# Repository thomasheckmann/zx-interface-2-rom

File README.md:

# ZX Interface 2 custom multi ROM catridge
Another custom ROM cartridge for ZX Interface 2, supporting 256kb EPROM with manual ROM selection using switch. The 256kb EPROM can hold up to 4 16kb banks, which is selectable with a switch combination.
This cartridge only supports 16KB images and manual bank switch and no paging out - it behaves just as the original ROM catridges.

## Schema and PCB version 1
Just a simple schema created with KiCad from description of original Interface 2 and Roms as found on the internet.

| SCHEMA | PCB |
| ------ | --- |
|||

Assembled the cartridge looks like this

## PCB version 1.1
Even that the first version of the PBC works ok, a few errors was made - but again I'm new to KiCad, so I'm slowly learning :-)

- Most important error is that I forgot to check the pads, I simply forgot to check that the pads are added to the solder mask layer! So as can be seen on the image, I had to carefully scrabe the surface - for the pads to be visible.

- The switch are "mirrored" in my oppinion, I would expect the left switch to be the most significant bit (MSB) - so another change for next version.

- Slot in connector turned out to be a bit too narrow, so I had to make it a bit wider.

- If you look closely vias are placed between the connector pads, in next version that will be avoided - by adding safe zones between all pads.

- Resistor value changed from 4K7 to 10K, suggested as the EEPROM is CMOS and not TTL.

- EEPROM rotated so it has same orientation as the other IC (stupid yes, but important to some like me)

- Changed PCB from 4 to 2 layers (Only used 4 to reduces the number of vias created between pads)

With these changes version 1.1 of this little PCB ends up like this:

| <!---> | <!---> |
| ------ | ------ |
|||

And here how it looks like when build and attached to a ZX Spectrum

| <!---> | <!---> |
| ------ | ------ |
|||

## How to create image for EEPROM
The W27C512 EEPROM can contain 4 x 16Kb images - selectable with the switch, forming the binary number 0-3 of the bank active.

For Windows
```
COPY /B ROM_3+ROM_2+ROM_1+ROM_0 IMAGE.BIN
```
Use your favorite (E)EPROM programmer to transfer the IMAGE.BIN to the EEPROM

```
LEFT|RIGHT
OFF | OFF - 0: ROM_0
OFF | ON  - 1: ROM_1
ON  | OFF - 2: ROM_2
ON  | ON  - 3: ROM_3
```
## PCB version 1.2
Only small changes to v1.2 of the board, which I think now can be considered final.

- Changed from pull-ups to pull-downs, to match actual behaviour of DIP-SWITCH (up = 1/ON/HIGH, down = 0/OFF/LOW)
- Made PADS 2mm longer, as some connectors might have issues with the smaller size

| SCHEMA | PCB |
| ------ | --- |
|||

## How to create image for EEPROM
The W27C512 EEPROM can contain 4 x 16Kb images - selectable with the switch, forming the binary number 0-3 of the bank active.

For Windows
```
COPY /B ROM_0+ROM_1+ROM_2+ROM_3 IMAGE.BIN
```
Use your favorite (E)EPROM programmer to transfer the IMAGE.BIN to the EEPROM
```
LEFT|RIGHT
OFF | OFF - 0: ROM_0
OFF | ON  - 1: ROM_1
ON  | OFF - 2: ROM_2
ON  | ON  - 3: ROM_3
```

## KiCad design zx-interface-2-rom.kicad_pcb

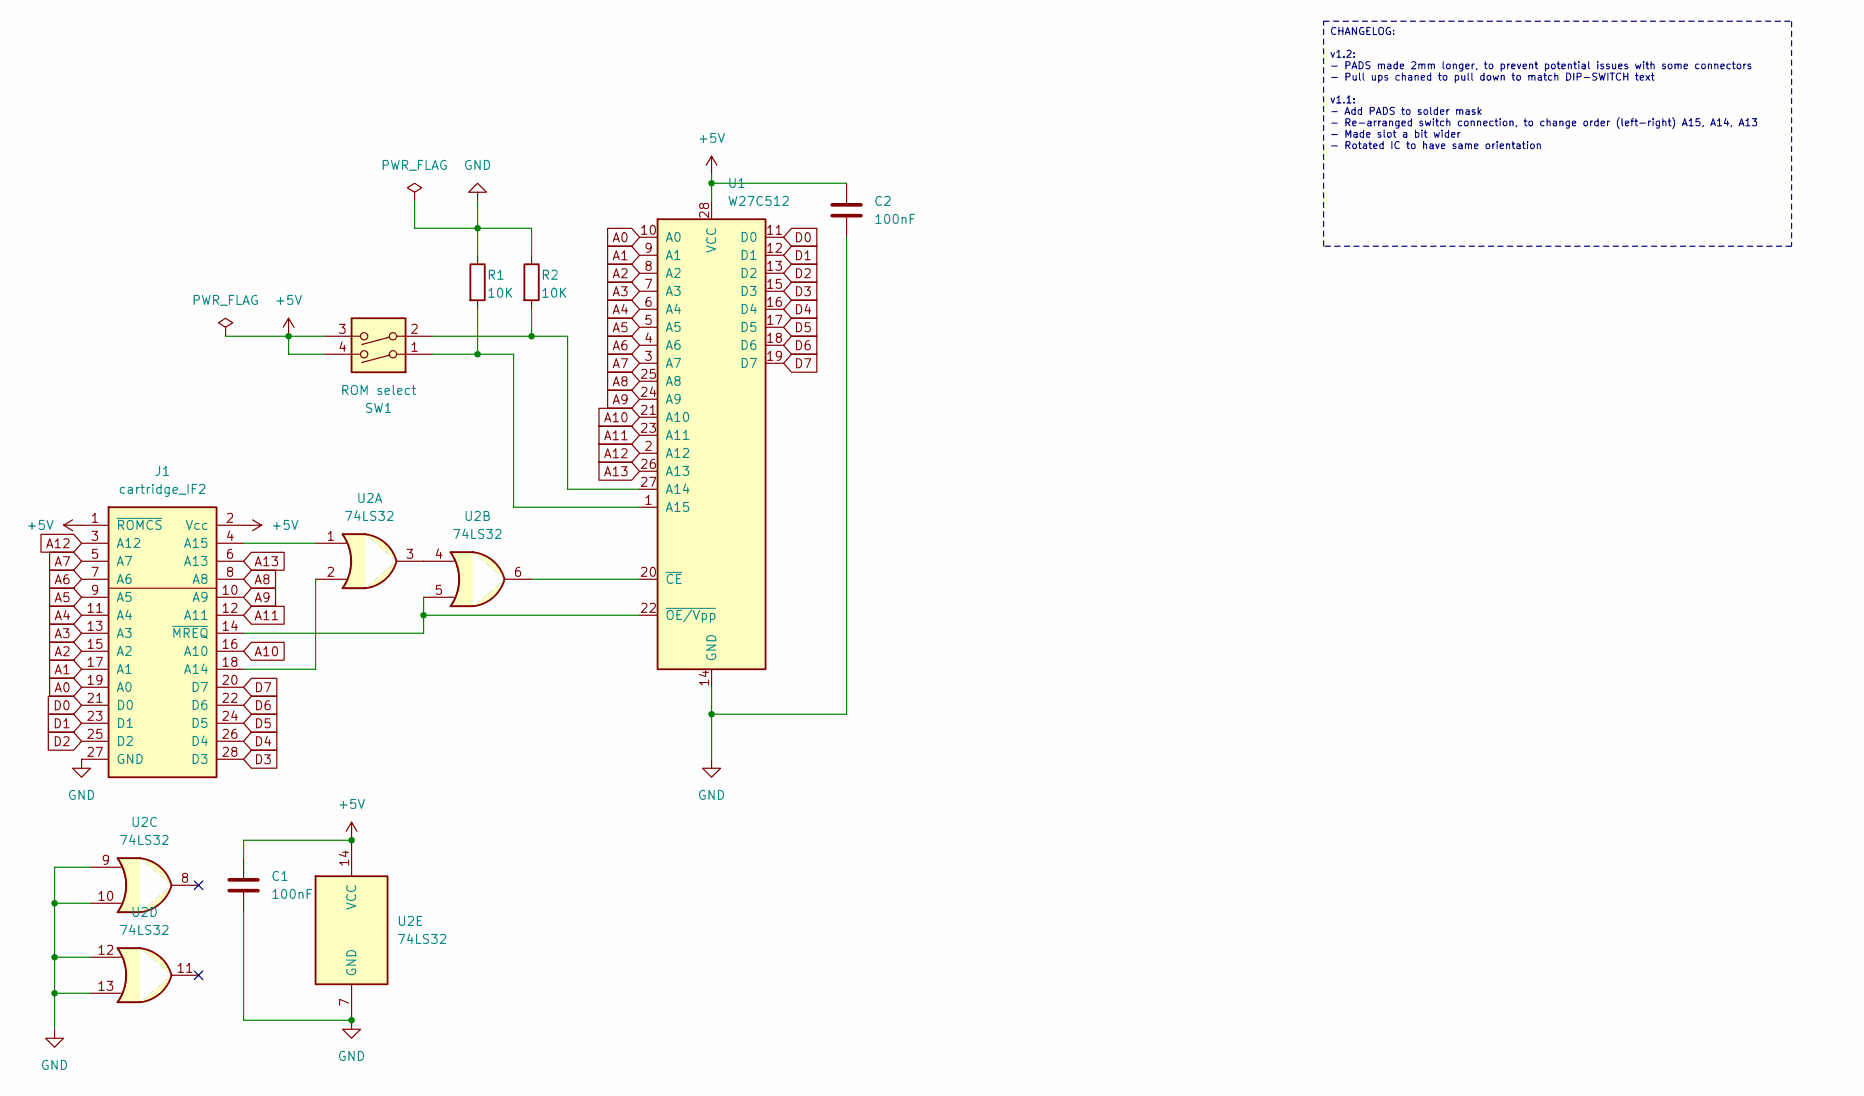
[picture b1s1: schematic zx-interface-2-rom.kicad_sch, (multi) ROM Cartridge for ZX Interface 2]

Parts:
C1, C2: 100nF; C_Disc_D3.0mm_W1.6mm_P2.50mm
J1: cartridge_IF2; CART_IF2_EDGE
R1, R2: 10K; R_Axial_DIN0207_L6.3mm_D2.5mm_P10.16mm_Horizontal
SW1: ROM select; SW_DIP_SPSTx02_Slide_6.7x6.64mm_W7.62mm_P2.54mm_LowProfile
U1: W27C512; DIP-28_W15.24mm_Socket
U2: 74LS32; DIP-14_W7.62mm_Socket

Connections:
+5V: C1.1, C2.1, J1.1 (~ROMCS), J1.2 (Vcc), SW1.3, SW1.4, U1.28 (VCC), U2.14 (VCC)
A0: J1.19 (A0), U1.10 (A0)
A1: J1.17 (A1), U1.9 (A1)
A2: J1.15 (A2), U1.8 (A2)
A3: J1.13 (A3), U1.7 (A3)
A4: J1.11 (A4), U1.6 (A4)
A5: J1.9 (A5), U1.5 (A5)
A6: J1.7 (A6), U1.4 (A6)
A7: J1.5 (A7), U1.3 (A7)
A8: J1.8 (A8), U1.25 (A8)
A9: J1.10 (A9), U1.24 (A9)
A10: J1.16 (A10), U1.21 (A10)
A11: J1.12 (A11), U1.23 (A11)
A12: J1.3 (A12), U1.2 (A12)
A13: J1.6 (A13), U1.26 (A13)
D0: J1.21 (D0), U1.11 (D0)
D1: J1.23 (D1), U1.12 (D1)
D2: J1.25 (D2), U1.13 (D2)
D3: J1.28 (D3), U1.15 (D3)
D4: J1.26 (D4), U1.16 (D4)
D5: J1.24 (D5), U1.17 (D5)
D6: J1.22 (D6), U1.18 (D6)
D7: J1.20 (D7), U1.19 (D7)
GND: C1.2, C2.2, J1.27 (GND), R1.1, R2.1, U1.14 (GND), U2.7 (GND), U2.9, U2.10, U2.12, U2.13
unnamed: J1.18 (A14), U2.2
unnamed: J1.4 (A15), U2.1
unnamed: J1.14 (~MREQ), U1.22 (~OE/Vpp), U2.5
unnamed: R2.2, SW1.2, U1.27 (A14)
unnamed: R1.2, SW1.1, U1.1 (A15)
unnamed: U1.20 (~CE), U2.6
unnamed: U2.3, U2.4

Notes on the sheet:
CHANGELOG: v1.2: - PADS made 2mm longer, to prevent potential issues with some connectors - Pull ups chaned to pull down to match DIP-SWITCH text v1.1: - Add PADS to solder mask - Re-arranged switch connection, to change order (left-right) A15, A14, A13 - Made slot a bit wider - Rotated IC to have 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

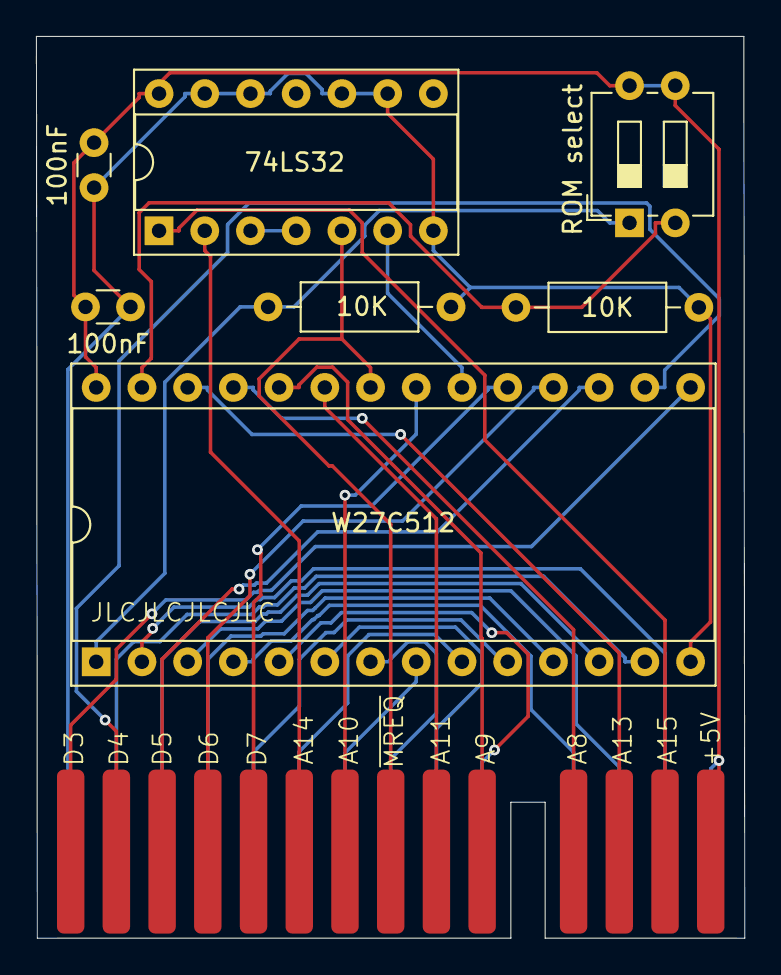
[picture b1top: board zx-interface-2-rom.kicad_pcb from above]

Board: 2 copper layers, 39.4 x 50.1 mm, 8 parts (1 on the bottom side), 31 nets.

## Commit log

2024-04-05 Initial version
2024-04-05 clean-up
2024-04-05 Added Gerbers
2024-04-08 .gitignore update
2024-04-14 Updated SYMBOL & FOOTPRINT library
2024-04-19 version 2 - added solder mask to pad
2024-04-19 Version 2 - final
2024-05-18 version 1.2
2024-05-21 Update README.md
    Updated for v1.2
